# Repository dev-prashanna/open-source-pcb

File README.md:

# Open Source PCB

Open hardware designs for a custom 8-bit CPU development board, ESP32 robotics, a brushed-motor flight controller, and a USB logic analyser.

## TIWARI

[TIWARI](TIWARI/) is a 50 × 35-mm, four-layer development board with an original
36MHz 8-bit CPU implemented in an iCE40UP5K FPGA, USB-C programming/serial,
16 digital GPIO, two hardware PWM outputs and a millisecond timer.

- [Beginner guide and project overview](TIWARI/README.md)
- [KiCad project](TIWARI/hardware/TIWARI.kicad_pro)
- [Fabrication and assembly package](TIWARI/fabrication/)
- [CPU architecture](TIWARI/docs/Architecture.md)
- [Verification evidence](TIWARI/docs/Verification.md)
- [Open-source licenses](TIWARI/LICENSE)

TW8-A0 passes ERC, DRC, schematic/PCB parity, CPU/peripheral HDL simulation,
and 36MHz FPGA timing checks for all four example images. This is an engineering
prototype; fabrication, assembly, USB/power qualification and real performance
measurements remain to be done. It uses its own instruction set and does not
run Arduino sketches.

## LogicScope S3

[LogicScope S3](LogicScope_S3/) is a compact 8-channel USB digital logic analyser hardware prototype built around the ESP32-S3, with a 55 x 40-mm, two-layer PCB.

- [Project documentation](LogicScope_S3/README.md)
- [KiCad project](LogicScope_S3/LogicScope_S3.kicad_pro)
- [Fabrication and assembly package](LogicScope_S3/fabrication/)
- [Engineering report](LogicScope_S3/docs/Engineering_Report.md)
- [Hardware validation plan](LogicScope_S3/docs/Validation_Plan.md)
- [License](LogicScope_S3/LICENSE)

LS-S3-A0 has recorded passing ERC, DRC, connectivity and schematic/PCB parity checks. Firmware and a simple desktop app v0.1.0 are implemented, with finite DMA captures, an eight-channel viewer, timing cursors and CSV/VCD export. Sampling performance and electrical behavior require physical prototype validation.

- [Firmware: build and flash](LogicScope_S3/firmware/README.md)
- [Desktop app: install and demo](LogicScope_S3/software/README.md)
- [Software verification](LogicScope_S3/docs/Software_Verification.md)

## RoveFlight S3

[RoveFlight S3](RoveFlight_S3/) is a 45 x 45-mm, six-layer ESP32-S3 controller for a 1S brushed quadcopter, with hardware motor interlocks, IMU, barometer, ToF and expansion interfaces.

- [Project documentation](RoveFlight_S3/README.md)
- [KiCad project](RoveFlight_S3/RoveFlight_S3.kicad_pro)
- [Fabrication and assembly package](RoveFlight_S3/fabrication/)
- [Manufacturing readiness and validation](RoveFlight_S3/docs/Manufacturing_Readiness.md)
- [License](RoveFlight_S3/LICENSE)

RF-S3-A0 passes ERC, DRC, connectivity and schematic/PCB parity checks. Via filling/capping and fabricator DFM are required; bench and flight qualification remain open.

## RoveCore One

The complete ESP32 robotics PCB project is in [RoveCore](RoveCore/).

- [Project documentation](RoveCore/README.md)
- [KiCad project](RoveCore/RoveCore_One.kicad_pro)
- [Fabrication files](RoveCore/fabrication/)
- [Manufacturing readiness](RoveCore/docs/Manufacturing_Readiness.md)
- [License](RoveCore/LICENSE)

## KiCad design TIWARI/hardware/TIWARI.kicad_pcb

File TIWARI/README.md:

# TIWARI — your CPU, your board

An original **8-bit processor development board** with reprogrammable hardware,
USB-C programming, a USB serial console, 16 digital GPIO, two hardware PWM
outputs, and a millisecond timer. The board measures **50 × 35 mm** and uses a
four-layer PCB with a chamfered outline.

**Engineering prototype:** the processor is simulated and the PCB files are
checked by software. No board has been manufactured or tested on a bench.
See [verification](docs/Verification.md) before ordering a prototype.

TIWARI is for learning how a processor works and building small digital control
projects. The CPU lives inside a Lattice iCE40UP5K FPGA: changing Verilog changes
its hardware. An FT2232H provides USB programming and a separate serial channel.
It is an original instruction set, not an AVR processor or an Arduino clone.

| Feature | TIWARI TW8-A0 |
| --- | --- |
| Processor | Original TIWARI-8, 36 MHz, 8-bit A/B registers and arithmetic |
| Program space | 4,096 × 16-bit instructions (8 KiB), initialized in FPGA image |
| Data memory | 256 bytes, separate from program memory |
| Expansion | 16 digital GPIO and 2 dedicated PWM pins, 3.3 V only |
| USB | USB-C, FT2232H channel A programming / channel B UART |
| Serial | 115200 baud, 8 data bits, no parity, 1 stop bit |
| Timer | 16-bit milliseconds with coherent snapshot |
| Physical | 50 × 35 mm, 4 copper layers, 1.0 mm nominal thickness |
| Firmware tools | Python assembler and open-source FPGA toolchain |

## Start here

1. [Beginner guide](docs/Getting_Started.md): understand the board, run tests,
   build a program, and program an assembled prototype.
2. [Instruction set](docs/Architecture.md) and [peripheral registers](docs/Peripherals.md).
3. [KiCad project](hardware/TIWARI.kicad_pro), [bill of materials](hardware/BOM.csv),
   [assembly and fabrication notes](docs/Hardware.md).
4. [Verification evidence](docs/Verification.md) and [hardware bring-up](docs/Bringup.md).

On a supported Linux machine with the dependencies installed:

```sh
make test sim
make synth                         # default: built-in LED blink
make flash PROGRAM=examples/serial_echo.asm
```

`make flash` writes the external configuration flash over USB. It does not
program one-time FPGA NVCM. The assembled board is required for that command.
The examples include blink, digital input mirroring, PWM, and serial echo.

## What makes TIWARI different

You can inspect and change the whole processor, rather than just its software.
PWM, GPIO synchronization, UART, and the timer run in parallel hardware. The
board has a separate CPU reset and FPGA reconfiguration button, built-in fault
indication, and rear service access to configuration signals.

The small PCB is about 52% smaller in area than the classic 68.6 × 53.4 mm Uno R3.
A higher clock is not a blanket application-speed comparison: instructions,
compiler availability, peripheral behavior, and workload matter. TIWARI does
not run Arduino sketches and has no C compiler, analog ADC, interrupts, or
Arduino shield compatibility in this revision. Its advantage is hardware you
can change; it does not replace the mature Arduino library ecosystem.

## Open source

Original hardware: CERN-OHL-P-2.0. Verilog, tools, tests, and examples: MIT.
Documentation: CC-BY-4.0. The KiCad-derived reviewed FPGA symbol retains its
upstream license and attribution. See [LICENSE](LICENSE) and
[library provenance](hardware/libraries/README.md).

Contributions are welcome through issues and pull requests. Please report
which PCB revision, program image, and tool versions you tested; distinguish
simulation results from measurements on a physical board.

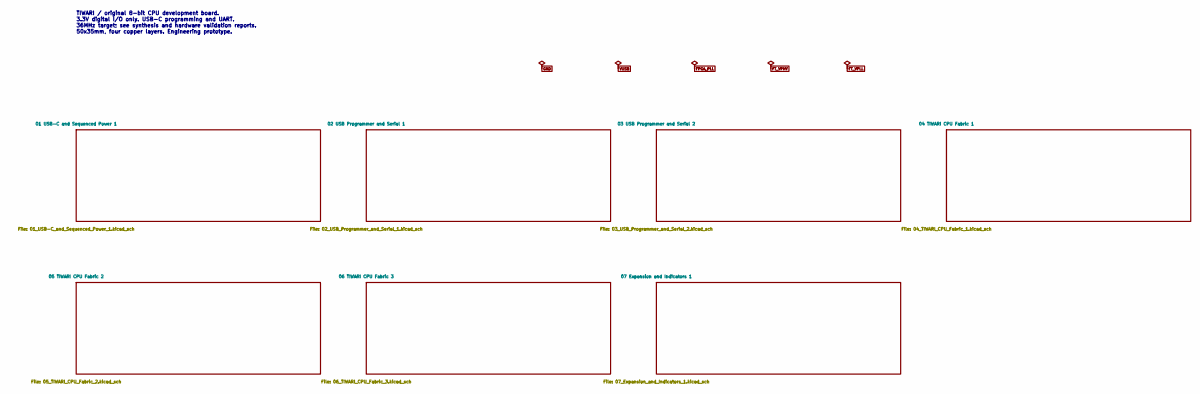
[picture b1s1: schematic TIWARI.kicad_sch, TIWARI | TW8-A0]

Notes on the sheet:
TIWARI / original 8-bit CPU development board. 3.3V digital I/O only. USB-C programming and UART. 36MHz target; see synthesis and hardware validation reports. 50x35mm, four copper layers. Engineering prototype.

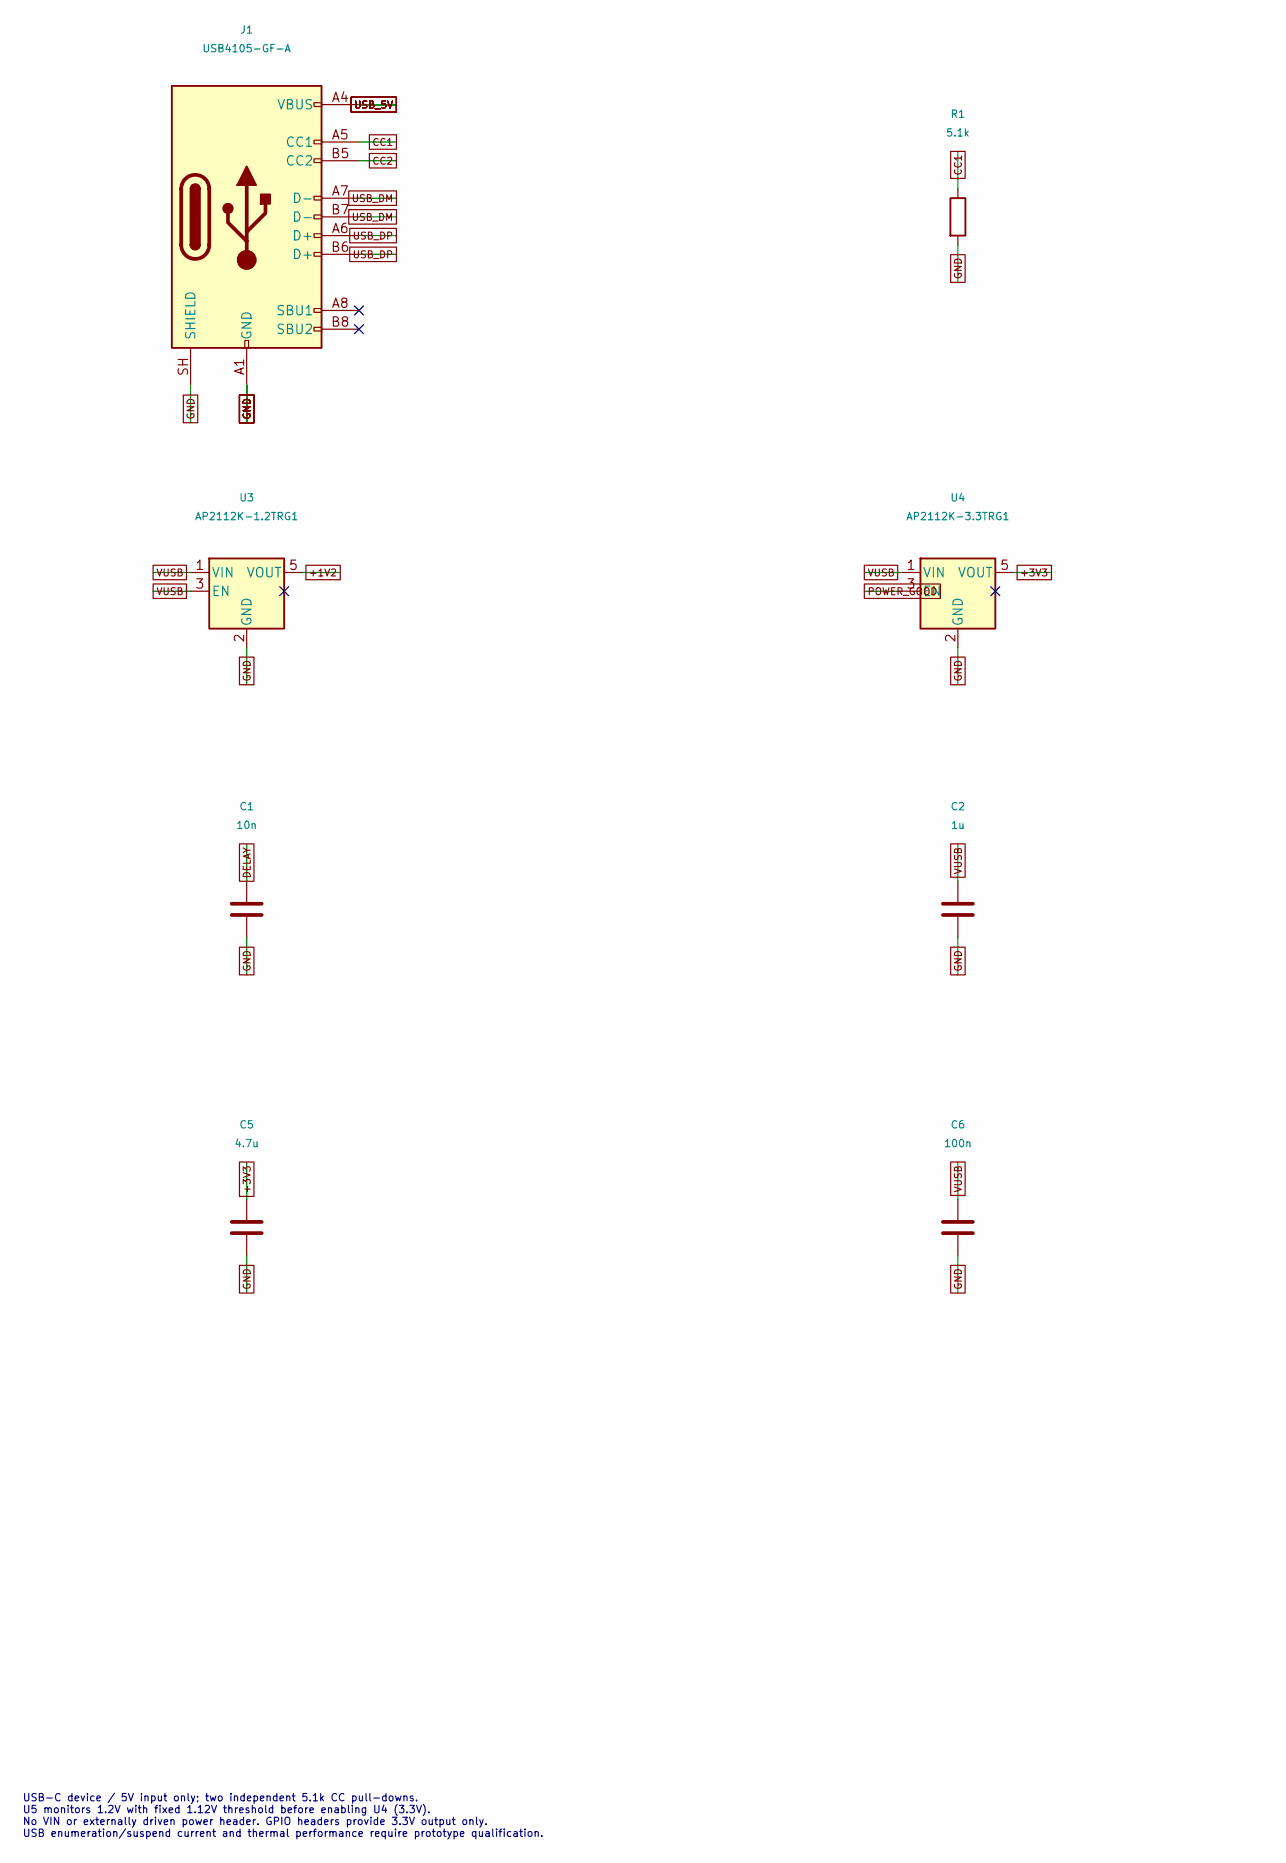
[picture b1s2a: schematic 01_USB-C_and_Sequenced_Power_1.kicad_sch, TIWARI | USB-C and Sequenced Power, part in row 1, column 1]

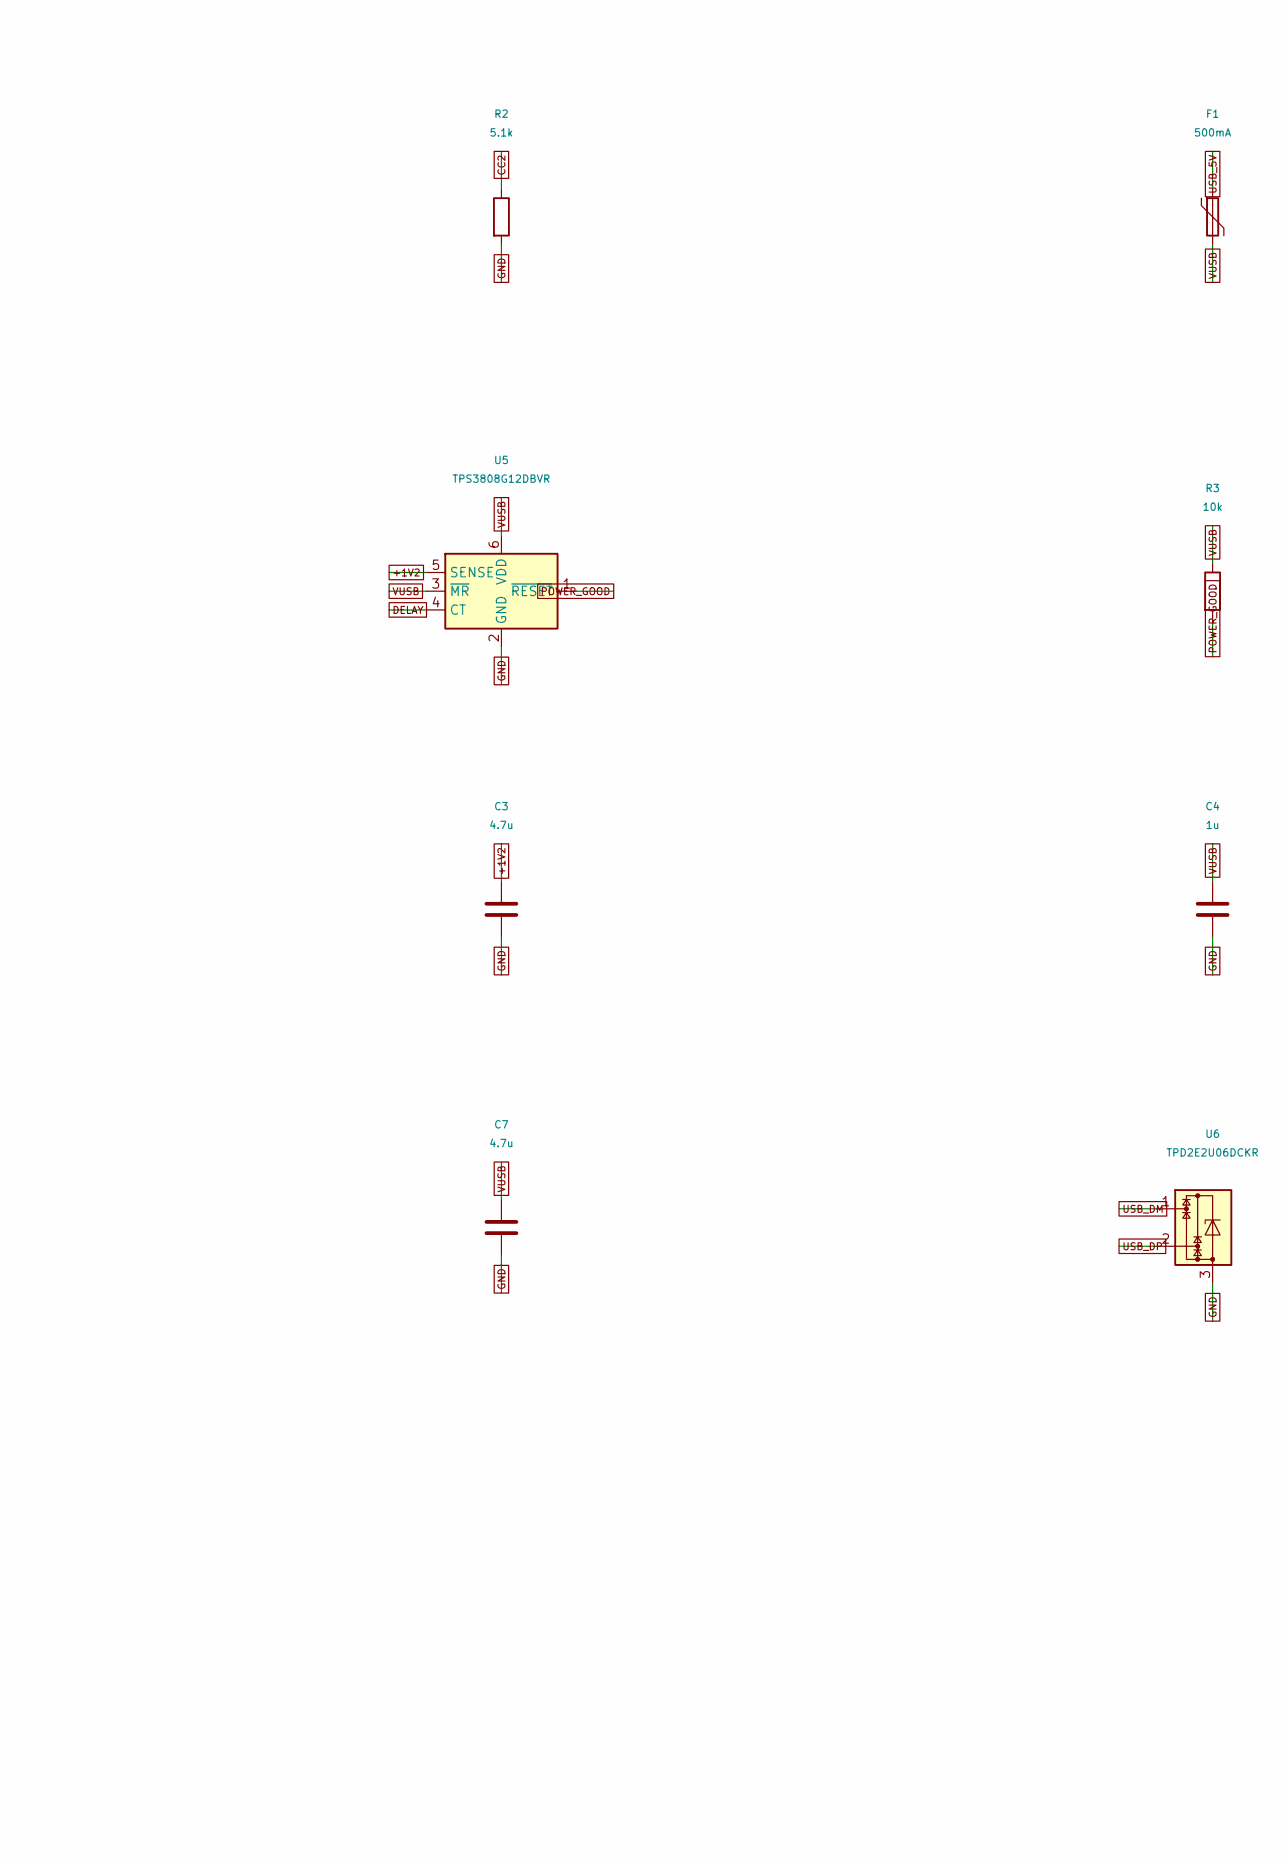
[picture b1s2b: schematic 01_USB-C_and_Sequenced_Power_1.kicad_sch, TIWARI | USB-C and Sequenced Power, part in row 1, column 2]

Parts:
C1: 10n; C_0603_1608Metric; MPN GRM188R71H103KA01D
C2, C4: 1u; C_0603_1608Metric; MPN GRM188R61A105KA61D
C3, C5, C7: 4.7u; C_0805_2012Metric; MPN GRM21BR61A475KA73L
C6: 100n; C_0603_1608Metric; MPN GRM188R71C104KA01D
F1: 500mA; Fuse_1206_3216Metric; MPN 1206L050YR
J1: USB4105-GF-A; USB_C_Receptacle_GCT_USB4105-xx-A_16P_TopMnt_Horizontal; MPN USB4105-GF-A
R1, R2: 5.1k; R_0603_1608Metric; MPN RC0603FR-075K1L
R3: 10k; R_0603_1608Metric; MPN RC0603FR-0710KL
U3: AP2112K-1.2TRG1; SOT-23-5; MPN AP2112K-1.2TRG1
U4: AP2112K-3.3TRG1; SOT-23-5; MPN AP2112K-3.3TRG1
U5: TPS3808G12DBVR; SOT-23-6; MPN TPS3808G12DBVR
U6: TPD2E2U06DCKR; SOT-353_SC-70-5; MPN TPD2E2U06DCKR

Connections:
+1V2: C3.1, U3.5 (VOUT), U5.5 (SENSE); also elsewhere on the board
+3V3: C5.1, U4.5 (VOUT); also elsewhere on the board
CC1: J1.A5 (CC1), R1.1
CC2: J1.B5 (CC2), R2.1
DELAY: C1.1, U5.4 (CT)
GND: C1.2, C2.2, C3.2, C4.2, C5.2, C6.2, C7.2, J1.A1 (GND), J1.A12 (GND), J1.B1 (GND), J1.B12 (GND), J1.SH (SHIELD), R1.2, R2.2, U3.2 (GND), U4.2 (GND), U5.2 (GND), U6.3; also elsewhere on the board
POWER_GOOD: R3.2, U4.3 (EN), U5.1 (~RESET)
USB_5V: F1.1, J1.A4 (VBUS), J1.A9 (VBUS), J1.B4 (VBUS), J1.B9 (VBUS)
USB_DM: J1.A7 (D-), J1.B7 (D-), U6.1; also elsewhere on the board
USB_DP: J1.A6 (D+), J1.B6 (D+), U6.2; also elsewhere on the board
VUSB: C2.1, C4.1, C6.1, C7.1, F1.2, R3.1, U3.1 (VIN), U3.3 (EN), U4.1 (VIN), U5.3 (~MR), U5.6 (VDD)

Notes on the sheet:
USB-C device / 5V input only; two independent 5.1k CC pull-downs. U5 monitors 1.2V with fixed 1.12V threshold before enabling U4 (3.3V). No VIN or externally driven power header. GPIO headers provide 3.3V output only. USB enumeration/suspend current and thermal performance require prototype qualifi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

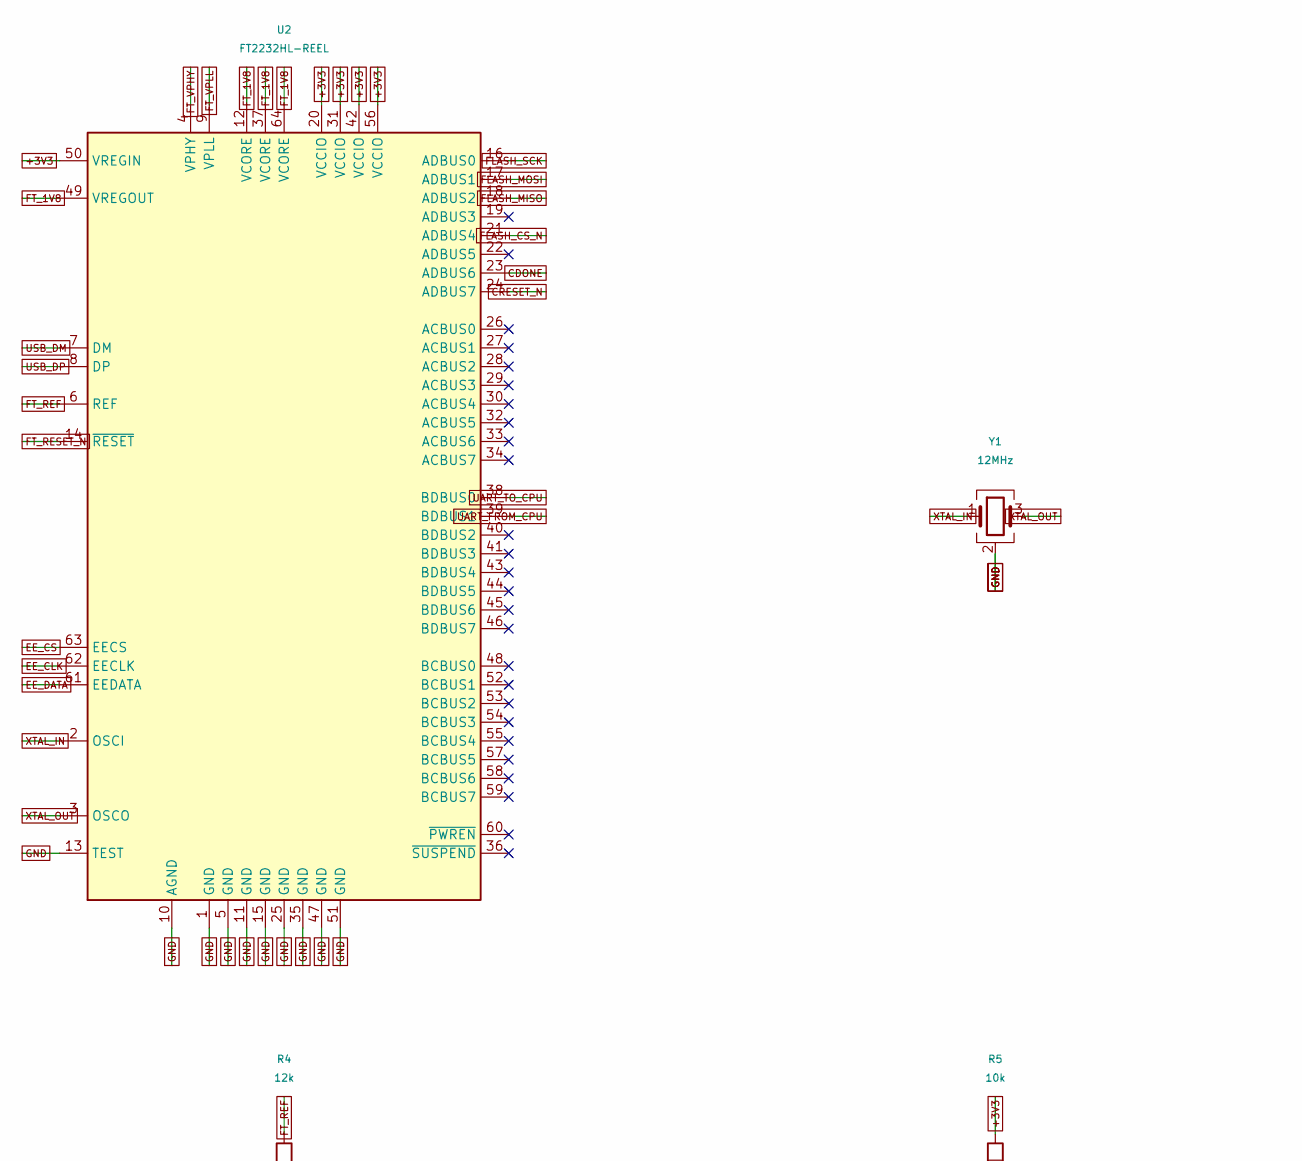
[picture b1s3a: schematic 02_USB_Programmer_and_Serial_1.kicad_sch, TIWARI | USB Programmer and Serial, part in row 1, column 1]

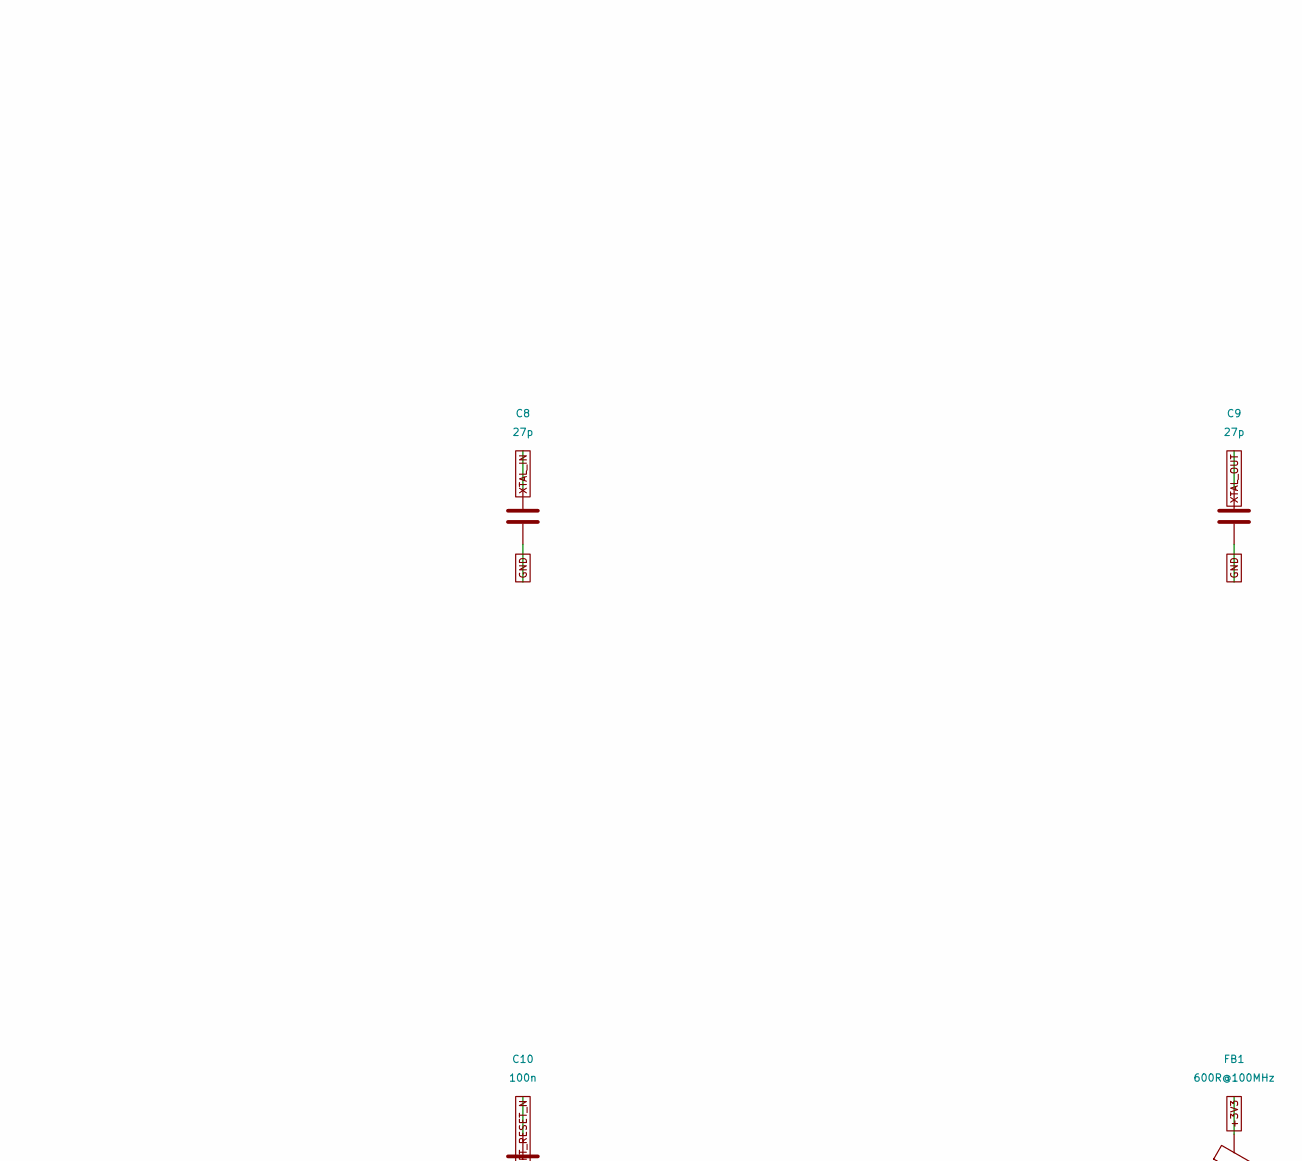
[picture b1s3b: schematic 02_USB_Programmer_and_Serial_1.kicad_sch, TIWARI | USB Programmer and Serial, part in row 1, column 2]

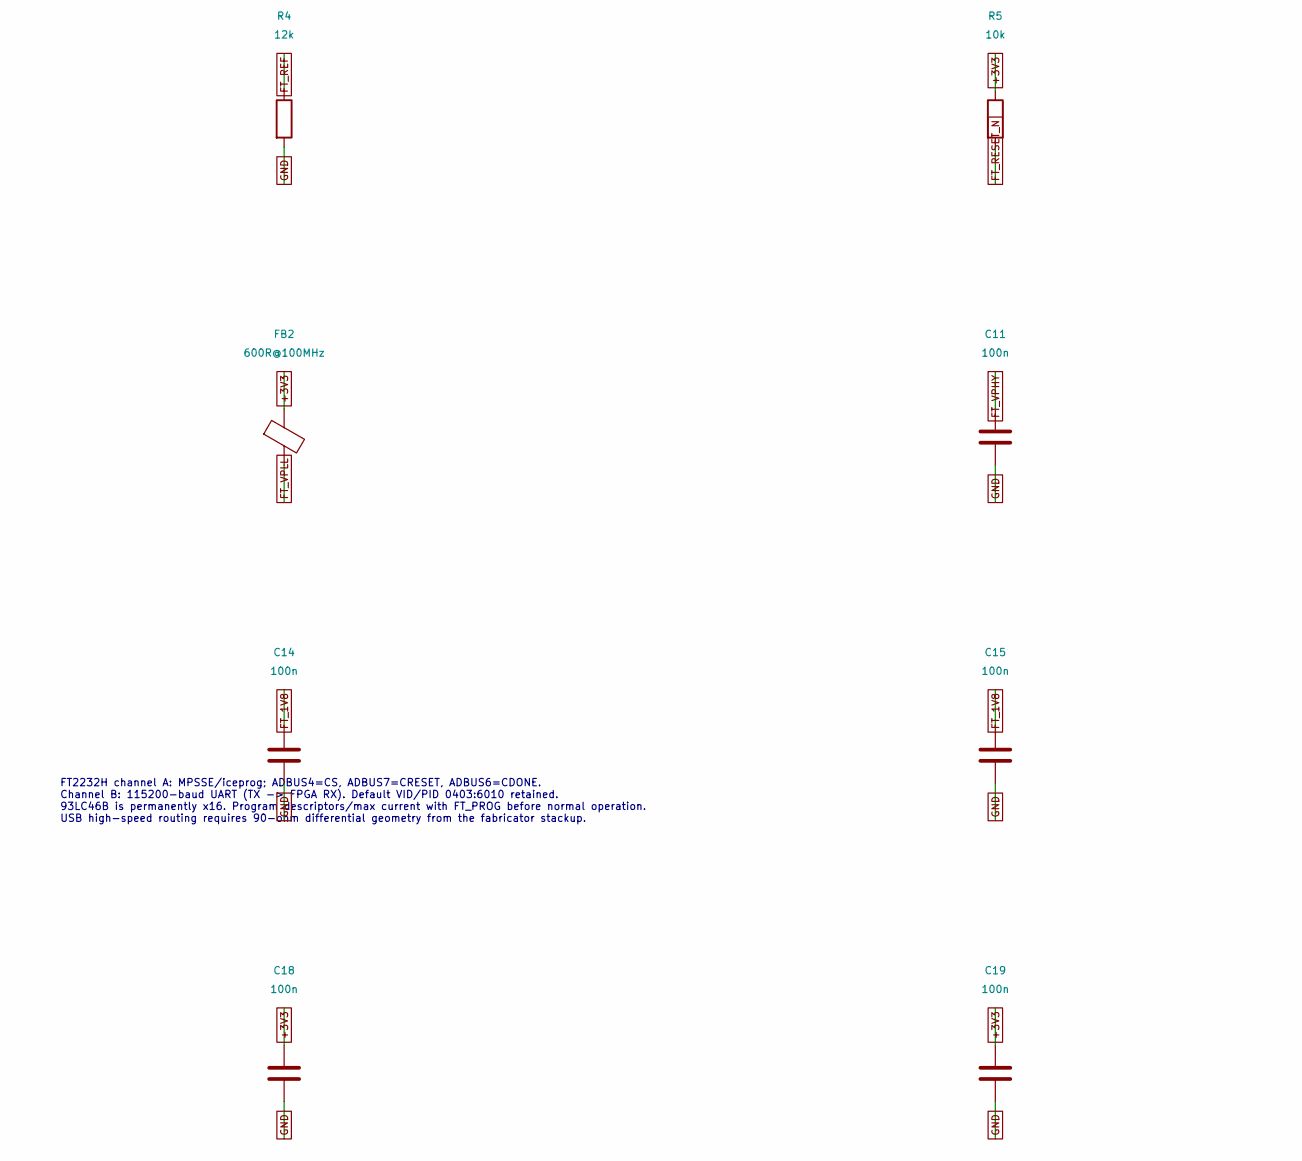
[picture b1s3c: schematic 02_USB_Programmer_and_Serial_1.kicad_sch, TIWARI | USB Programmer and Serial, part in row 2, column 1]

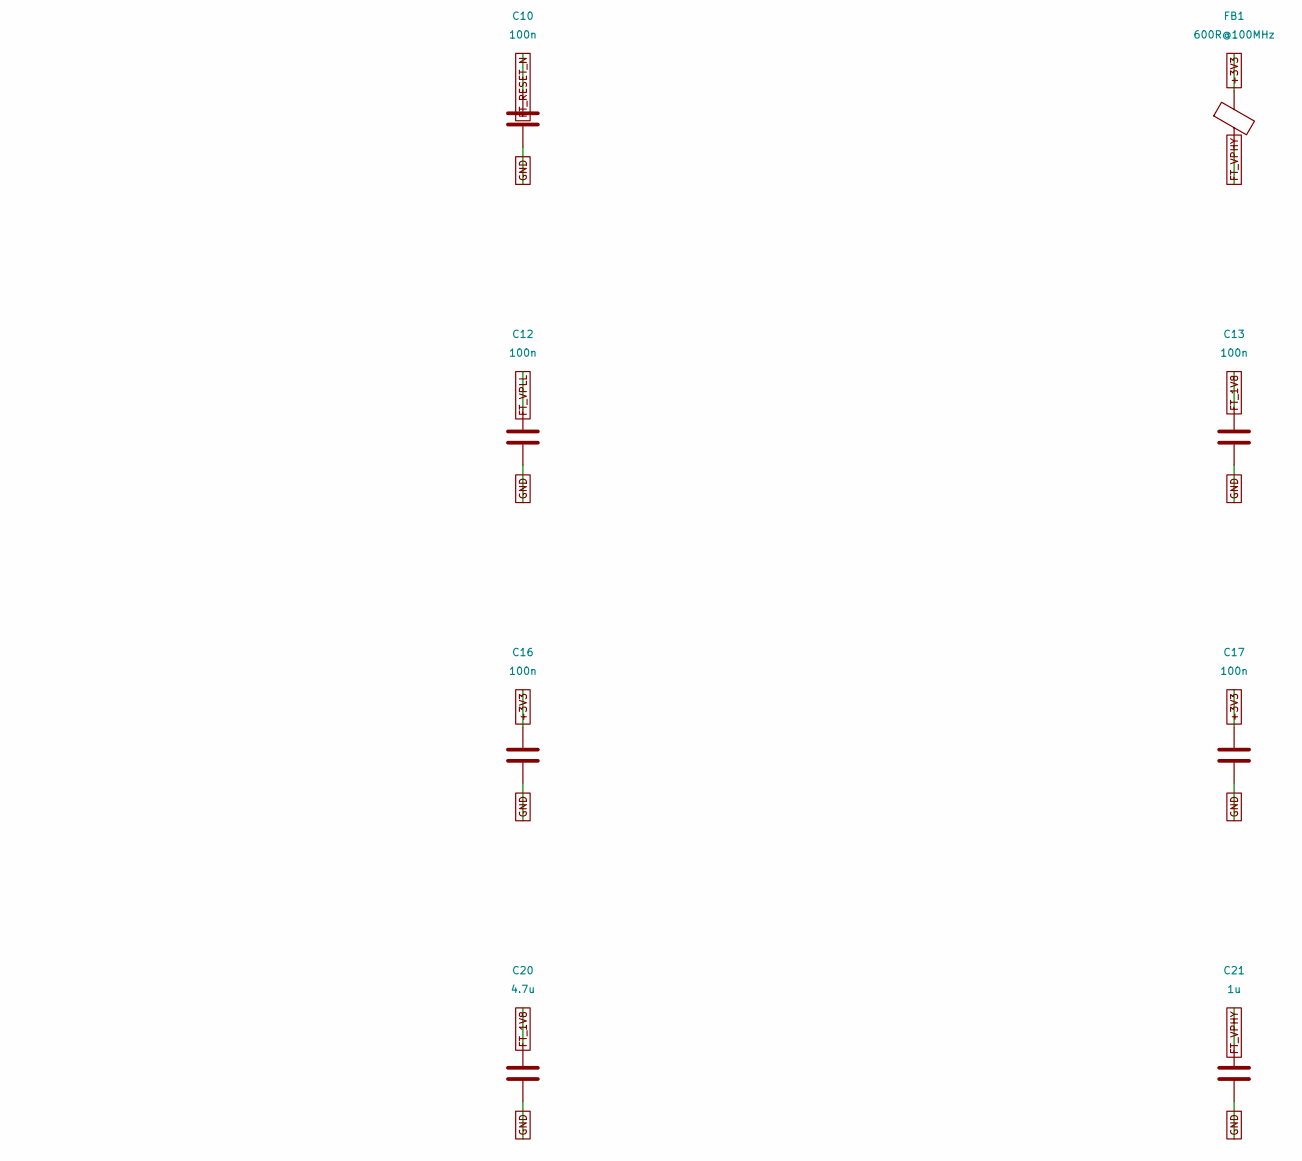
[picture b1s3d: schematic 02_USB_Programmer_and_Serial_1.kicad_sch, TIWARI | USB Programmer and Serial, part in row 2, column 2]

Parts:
C8, C9: 27p; C_0603_1608Metric; MPN GRM1885C1H270JA01D
C10, C11, C12, C13, C14, C15, C16, C17, C18, C19: 100n; C_0603_1608Metric; MPN GRM188R71C104KA01D
C20: 4.7u; C_0805_2012Metric; MPN GRM21BR61A475KA73L
C21: 1u; C_0603_1608Metric; MPN GRM188R61A105KA61D
FB1, FB2: 600R@100MHz; L_0603_1608Metric; MPN BLM18AG601SN1D
R4: 12k; R_0603_1608Metric; MPN RC0603FR-0712KL
R5: 10k; R_0603_1608Metric; MPN RC0603FR-0710KL
U2: FT2232HL-REEL; LQFP-64_10x10mm_P0.5mm; MPN FT2232HL-REEL
Y1: 12MHz; Crystal_SMD_3225-4Pin_3.2x2.5mm; MPN ABM8-12.000MHZ-B2-T

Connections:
+3V3: C16.1, C17.1, C18.1, C19.1, FB1.1, FB2.1, R5.1, U2.20 (VCCIO), U2.31 (VCCIO), U2.42 (VCCIO), U2.50 (VREGIN), U2.56 (VCCIO); also elsewhere on the board
CDONE: U2.23 (ADBUS6); also elsewhere on the board
CRESET_N: U2.24 (ADBUS7); also elsewhere on the board
EE_CLK: U2.62 (EECLK); also elsewhere on the board
EE_CS: U2.63 (EECS); also elsewhere on the board
EE_DATA: U2.61 (EEDATA); also elsewhere on the board
FLASH_CS_N: U2.21 (ADBUS4); also elsewhere on the board
FLASH_MISO: U2.18 (ADBUS2); also elsewhere on the board
FLASH_MOSI: U2.17 (ADBUS1); also elsewhere on the board
FLASH_SCK: U2.16 (ADBUS0); also elsewhere on the board
FT_1V8: C13.1, C14.1, C15.1, C20.1, U2.12 (VCORE), U2.37 (VCORE), U2.49 (VREGOUT), U2.64 (VCORE)
FT_REF: R4.1, U2.6 (REF)
FT_RESET_N: C10.1, R5.2, U2.14 (~RESET)
FT_VPHY: C11.1, C21.1, FB1.2, U2.4 (VPHY)
FT_VPLL: C12.1, FB2.2, U2.9 (VPLL)
GND: C8.2, C9.2, C10.2, C11.2, C12.2, C13.2, C14.2, C15.2, C16.2, C17.2, C18.2, C19.2, C20.2, C21.2, R4.2, U2.1 (GND), U2.5 (GND), U2.10 (AGND), U2.11 (GND), U2.13 (TEST), U2.15 (GND), U2.25 (GND), U2.35 (GND), U2.47 (GND), U2.51 (GND), Y1.2 (G), Y1.4 (G); also elsewhere on the board
UART_FROM_CPU: U2.39 (BDBUS1); also elsewhere on the board
UART_TO_CPU: U2.38 (BDBUS0); also elsewhere on the board
USB_DM: U2.7 (DM); also elsewhere on the board
USB_DP: U2.8 (DP); also elsewhere on the board
XTAL_IN: C8.1, U2.2 (OSCI), Y1.1
XTAL_OUT: C9.1, U2.3 (OSCO), Y1.3

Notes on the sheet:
FT2232H channel A: MPSSE/iceprog; ADBUS4=CS, ADBUS7=CRESET, ADBUS6=CDONE. Channel B: 115200-baud UART (TX -> FPGA RX). Default VID/PID 0403:6010 retained. 93LC46B is permanently x16. Program descriptors/max current with FT_PROG before normal operation. USB high-speed routing requires 90-ohm differe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

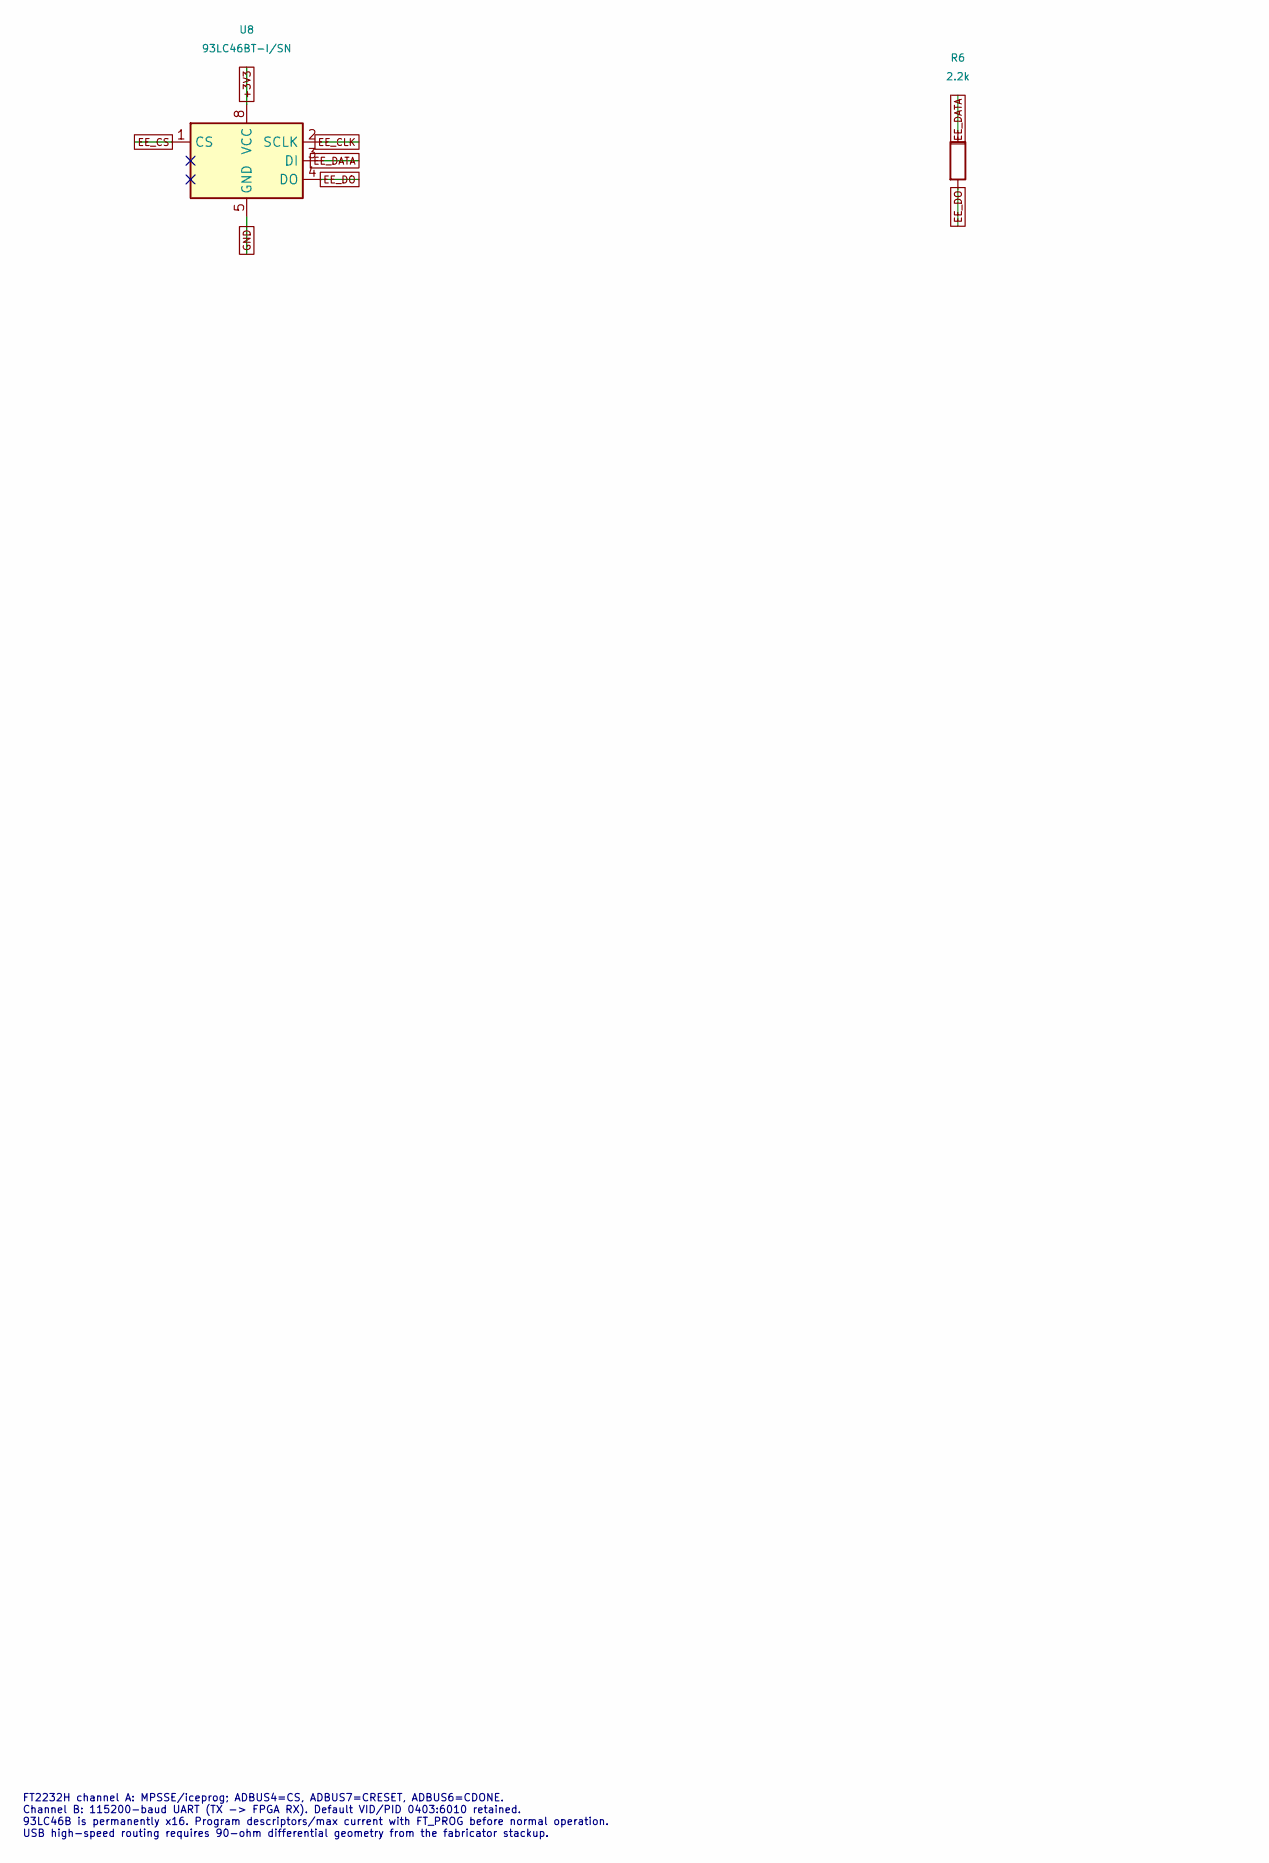
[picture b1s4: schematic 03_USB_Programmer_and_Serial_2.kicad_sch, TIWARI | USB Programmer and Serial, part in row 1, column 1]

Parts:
C22: 100n; C_0603_1608Metric; MPN GRM188R71C104KA01D
R6: 2.2k; R_0603_1608Metric; MPN RC0603FR-072K2L
R7: 10k; R_0603_1608Metric; MPN RC0603FR-0710KL
U8: 93LC46BT-I/SN; SOIC-8_3.9x4.9mm_P1.27mm; MPN 93LC46BT-I/SN

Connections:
+3V3: C22.1, R7.1, U8.8 (VCC); also elsewhere on the board
EE_CLK: U8.2 (SCLK); also elsewhere on the board
EE_CS: U8.1 (CS); also elsewhere on the board
EE_DATA: R6.1, R7.2, U8.3 (DI); also elsewhere on the board
EE_DO: R6.2, U8.4 (DO)
GND: C22.2, U8.5 (GND); also elsewhere on the board

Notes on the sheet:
FT2232H channel A: MPSSE/iceprog; ADBUS4=CS, ADBUS7=CRESET, ADBUS6=CDONE. Channel B: 115200-baud UART (TX -> FPGA RX). Default VID/PID 0403:6010 retained. 93LC46B is permanently x16. Program descriptors/max current with FT_PROG before normal operation. USB high-speed routing requires 90-ohm differe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
